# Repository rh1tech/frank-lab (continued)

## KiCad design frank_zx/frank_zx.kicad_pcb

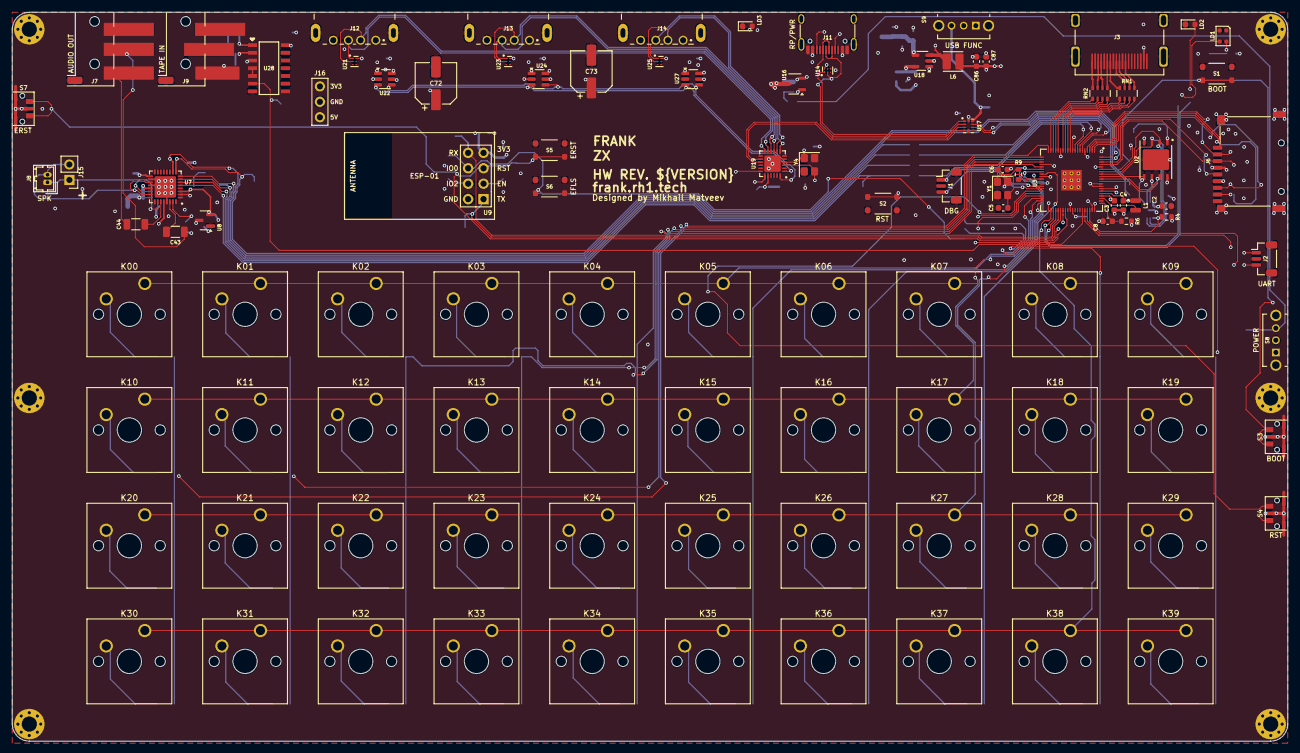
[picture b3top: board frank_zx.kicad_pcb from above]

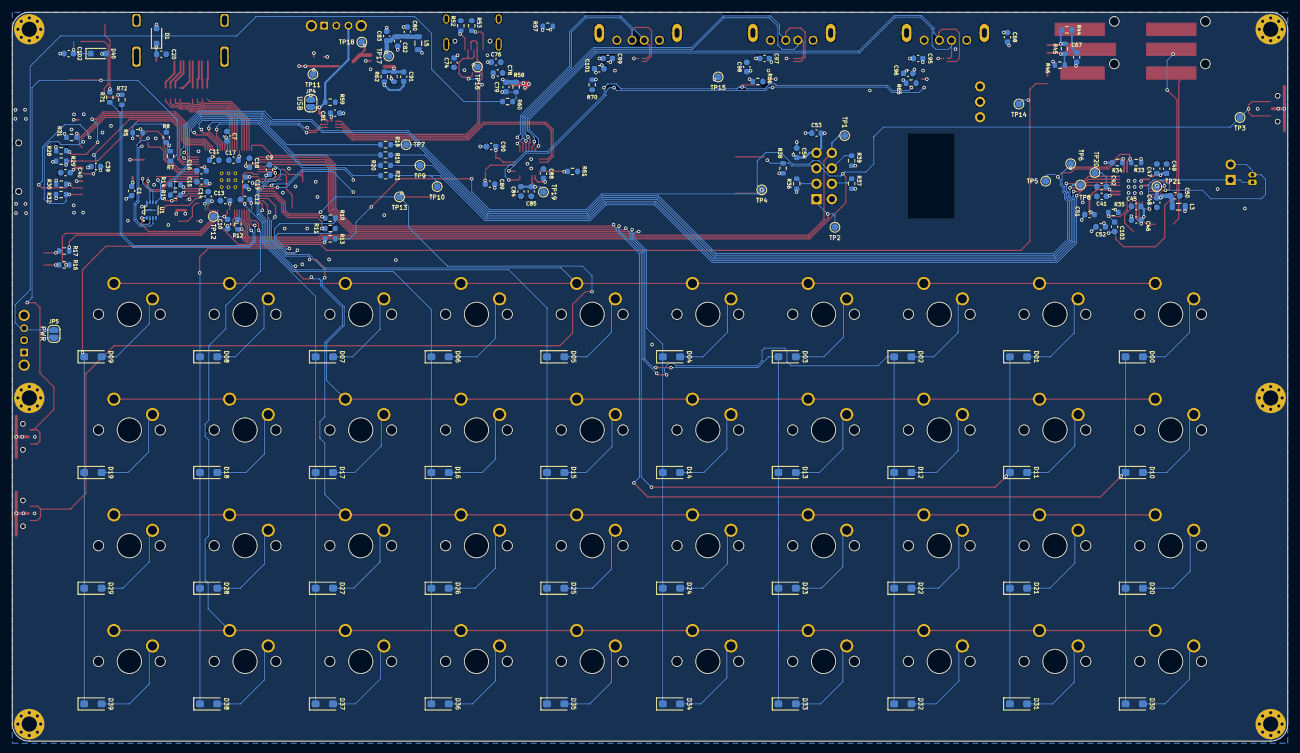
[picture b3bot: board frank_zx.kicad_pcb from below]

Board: 4 copper layers, 210.0 x 120.0 mm, 273 parts (164 on the bottom side), 179 nets.

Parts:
C1, C2, C7, C10, C11, C12, C13, C14, C15, C16, C17, C18, C19, C20, C40, C41, C42, C46, C49, C50, C54, C67, C68, C74, C79, C81, C83, C95, C97, C99, C102: 100nF; C_0603_1608Metric
C3, C4, C8, C9: 4.7uF; C_0603_1608Metric
C5, C6: 15pF; C_0603_1608Metric
C39, C45, C47, C48, C53, C76, C78, C80, C82, C84, C86, C87, C88, C96, C98, C101, C103: 10uF; C_0603_1608Metric
C43, C44: 100uF; C_1206_3216Metric
C51, C52, C85: 1uF; C_0603_1608Metric
C72, C73: 100uF; CP_Elec_6.3x6.0
C89, C90: 12pF; C_0603_1608Metric
C91: 22pF; C_0603_1608Metric
D00, D01, D02, D03, D04, D05, D06, D07, D08, D09, D10, D11, D12, D13, D14, D15, D16, D17, D18, D19, D20, D21, D22, D23, D24, D25, D26, D27, D28, D29, D30, D31, D32, D33, D34, D35, D36, D37, D38, D39: 1N4148W; D_SOD-123
D1, D40: 1N5819WS; D_SOD-323
H1, H2, H3, H4, H5, H6: MountingHole; MountingHole_2.5mm_Pad_Via
J1: Debug; JST_SH_1x03_P1.00mm_Vertical
J2: UART; JST_SH_1x03_P1.00mm_Vertical
J3: HDMI-001 19PCBTP; HDMI_Female
J6: 104031-0811; MicroSD_SMD_Long
J7: PJ-320D; AudioJack_3.5mm_PJ320D_AudioOut
J8: DF13-2P-1.25DSA; Hirose_DF13-02P-1.25DSA
J9: PJ-320D; AudioJack_3.5mm_PJ320D_TapeIn
J11: USB4215-03-A; USB_C_Receptacle
J12, J13, J14: AF 10.0 HC6.3; USB_A_Short
J15: Speaker; PinHeader_1x02_P2.54mm_Vertical
J16: PWR; PinHeader_1x03_P2.54mm
JP4: USB Debug; SolderJumper-2_P1.3mm_Open_RoundedPad1.0x1.5mm
JP5: PWR Debug; SolderJumper-2_P1.3mm_Open_RoundedPad1.0x1.5mm
K00, K01, K02, K03, K04, K05, K06, K07, K08, K09, K10, K11, K12, K13, K14, K15, K16, K17, K18, K19, K20, K21, K22, K23, K24, K25, K26, K27, K28, K29, K30, K31, K32, K33, K34, K35, K36, K37, K38, K39: MX; SW_Cherry_MX_1.00u_PCB
L1: 3.3µH; L_AOTA-B201610_2.0x1.6mm
L3, L5: 330R 2A; L_0805_2012Metric
L6: 2.2uH; L_Cenker_CKCS3015
LD1: WS2812B-2020; LED_WS2812B-2020_PLCC4_2.0x2.0mm
LD2: Blue; LED_0603_1608Metric
LD3: Green; LED_0603_1608Metric
R4, R5, R28, R29, R30, R31, R32, R35, R36, R37, R59, R60: 10K; R_0603_1608Metric
R6, R18, R19, R20, R21: 33R; R_0603_1608Metric
R7, R9, R57, R71: 1K; R_0603_1608Metric
R8: 0R; R_0603_1608Metric
R10, R11, R12, R13, R16, R17: 100R; R_0603_1608Metric
R14, R15: 27R; R_0603_1608Metric
R33, R34, R38, R39, R44, R61: 4.7K; R_0603_1608Metric
R45, R46, R58, R62, R65, R66, R70: 100K; R_0603_1608Metric
R52, R53: 5.1K; R_0603_1608Metric
R63: 22K; R_0603_1608Metric
R72: 330R; R_0603_1608Metric
RN1, RN2: 270R; R_Array_4x0603
S1: RP Boot; Button_SMD_3x4x2mm
S2: RP Reset; Button_SMD_3x4x2mm
S3: RP Boot; Button_SMD_TS1234VW
S4: RP Reset; Button_SMD_TS1234VW
S5: ESP Reset; Button_SMD_3x4x2mm
S6: ESP Flash; Button_SMD_3x4x2mm
S7: ESP Reset; Button_SMD_TS1234VW
S8, S9: SK12D07VG3NS; Switch_Slide_SK12D07VG3NS_PWR
TP1: GPIO36/TX; TestPoint_Pad_D1.2mm
TP2: GPIO37/RX; TestPoint_Pad_D1.2mm
TP3: GPIO38/ESP_RST; TestPoint_Pad_D1.2mm
TP4: GPIO39/ESP_BOOT; TestPoint_Pad_D1.2mm
TP5: GPIO2/SDA; TestPoint_Pad_D1.2mm
TP6: GPIO3/SCL; TestPoint_Pad_D1.2mm
TP7: GPIO8/MCLK; TestPoint_Pad_D1.2mm
TP8: GPIO9/BCLK; TestPoint_Pad_D1.2mm
TP9: GPIO10/WCLK; TestPoint_Pad_D1.2mm
TP10: GPIO11/DIN; TestPoint_Pad_D1.2mm
TP11: +3V3; TestPoint_Pad_D1.2mm
TP12: +1V1; TestPoint_Pad_D1.2mm
TP13: RUN; TestPoint_Pad_D1.2mm
TP14: GPIO44; TestPoint_Pad_D1.2mm
TP15: VBUS; TestPoint_Pad_D1.2mm
TP16: VBUS_IN; TestPoint_Pad_D1.2mm
TP17: +5V_BUCK; TestPoint_Pad_D1.2mm
TP18: LX; TestPoint_Pad_D1.2mm
TP19: VDD33; TestPoint_Pad_D1.2mm
TP20: +1V8; TestPoint_Pad_D1.2mm
TP21: +5V_SPK; TestPoint_Pad_D1.2mm
U1: APS6404L-3SQR-ZR; PSON50P200X300X50-9N
U2: W25Q128JVPIQ; WSON-8-1EP_6x5mm_P1.27mm_EP3.45x4.35mm
U3: RP2350B; RP2350-QFN-80_10x10_P0.4mm
U7: TLV320DAC3100IRHBR
U8: XC6206P182MR-G; SOT-23
U9: ESP-01v090; ESP-01S
U14, U21, U23, U25: TPD4S012DRYR
U16: AO3401A; SOT-23-3L_AOS
U17: TS3USB221RSER; UQFN-10
U18: SY8089AAAC; SOT-23-5
U19: CH334F; QFN-24-1EP_4x4mm_P0.5mm_EP2.7x2.7mm
U22, U24, U27: CH217K; SOT-23-6
U28: CD4069UBM; SOIC127P600X175-14N
Y1, Y4: 12 MHz; Crystal_SMD_3225-4Pin_3.2x2.5mm

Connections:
+1V1: C4.1, C7.1, C9.1, C10.1, L1.1, TP12.1, U3.10 (DVDD), U3.32 (DVDD), U3.51 (DVDD), U3.65 (VREG_FB)
+1V8: C42.2, C51.2, TP20.1, U7.3 (DVDD), U8.2 (VOUT)
+3V3: C1.1, C2.2, C3.1, C11.1, C12.1, C13.1, C14.1, C15.1, C16.1, C17.1, C18.1, C19.1, C39.2, C40.2, C41.1, C45.2, C46.2, C47.2, C49.2, C52.2, C53.1, C54.1, C68.1, C81.2, C86.1, C87.1, C91.1, J6.4 (VDD), J16.1, JP4.1 (A), L6.1, R4.2, R5.2, R6.1, R28.1, R29.1, R30.1, R31.2, R32.1, R33.2, R34.2, R35.2, R36.1, R37.1, R38.1, R39.1, R57.2, R62.1, S9.2, TP11.1, U1.8 (VDD), U2.8 (VCC), U3.5 (IOVDD), U3.15 (IOVDD), U3.24 (IOVDD), U3.29 (IOVDD), U3.41 (IOVDD), U3.50 (IOVDD), U3.59 (ADC_AVDD), U3.60 (IOVDD), U3.64 (VREG_VIN), U3.68 (USB_OTP_VDD), U3.69 (QSPI_IOVDD), U3.76 (IOVDD), U7.2 (IOVDD), U7.17 (AVDD), U7.28 (HPVDD), U8.3 (VIN), U9.7 (VCC), U17.10 (VCC), U28.14 (VDD)
/Audio/+5V_SPK: C48.2, C50.2, L3.1, TP21.1, U7.21 (SPKVDD_1), U7.24 (SPKVDD_2)
/Audio/CODEC_RST: C103.1, R35.1, U7.31 (~RESET)
/Audio/SPKM: J8.2, J15.2, U7.19 (SPKM_1), U7.23 (SPKM_2)
/Audio/SPKP: J8.1, J15.1, U7.22 (SPKP_1), U7.26 (SPKP_2)
/ESP01/CH_PD: R36.2, U9.3 (CH_PD)
/GPIO2/SDA: R34.1, TP5.1, U3.79 (GPIO2), U7.9 (SDA)
/GPIO3/SCL: R33.1, TP6.1, U3.80 (GPIO3), U7.10 (SCL)
/GPIO8/MCLK: R18.2, TP7.1, U7.8 (MCLK)
/GPIO9/BCLK: R19.2, TP8.1, U7.7 (BCLK)
/GPIO10/WCLK: R20.2, TP9.1, U7.6 (WCLK)
/GPIO11/DIN: R21.2, TP10.1, U7.5 (DIN)
/GPIO12/CLKN: RN1.4 (R4.1), U3.11 (GPIO12)
/GPIO13/CLKP: RN1.3 (R3.1), U3.12 (GPIO13)
/GPIO14/D0N: RN1.2 (R2.1), U3.13 (GPIO14)
/GPIO15/D0P: RN1.1 (R1.1), U3.14 (GPIO15)
/GPIO16/D1N: RN2.4 (R4.1), U3.16 (GPIO16)
/GPIO17/D1P: RN2.3 (R3.1), U3.17 (GPIO17)
/GPIO18/D2N: RN2.2 (R2.1), U3.18 (GPIO18)
/GPIO19/D2P: RN2.1 (R1.1), U3.19 (GPIO19)
/GPIO20/COL0: D00.1 (K), D10.1 (K), D20.1 (K), D30.1 (K), U3.20 (GPIO20)
/GPIO21/COL1: D01.1 (K), D11.1 (K), D21.1 (K), D31.1 (K), U3.21 (GPIO21)
/GPIO22/COL2: D02.1 (K), D12.1 (K), D22.1 (K), D32.1 (K), U3.22 (GPIO22)
/GPIO23/COL3: D03.1 (K), D13.1 (K), D23.1 (K), D33.1 (K), U3.23 (GPIO23)
/GPIO24/COL4: D04.1 (K), D14.1 (K), D24.1 (K), D34.1 (K), U3.25 (GPIO24)
/GPIO25/COL5: D05.1 (K), D15.1 (K), D25.1 (K), D35.1 (K), U3.26 (GPIO25)
/GPIO26/COL6: D06.1 (K), D16.1 (K), D26.1 (K), D36.1 (K), U3.27 (GPIO26)
/GPIO27/COL7: D07.1 (K), D17.1 (K), D27.1 (K), D37.1 (K), U3.28 (GPIO27)
/GPIO28/COL8: D08.1 (K), D18.1 (K), D28.1 (K), D38.1 (K), R10.2
/GPIO29/COL9: D09.1 (K), D19.1 (K), D29.1 (K), D39.1 (K), R11.2
/GPIO30/ROW0: K00.1, K01.1, K02.1, K03.1, K04.1, K05.1, K06.1, K07.1, K08.1, K09.1, U3.38 (GPIO30)
/GPIO31/ROW1: K10.1, K11.1, K12.1, K13.1, K14.1, K15.1, K16.1, K17.1, K18.1, K19.1, U3.39 (GPIO31)
/GPIO32/ROW2: K20.1, K21.1, K22.1, K23.1, K24.1, K25.1, K26.1, K27.1, K28.1, K29.1, U3.40 (GPIO32)
/GPIO33/ROW3: K30.1, K31.1, K32.1, K33.1, K34.1, K35.1, K36.1, K37.1, K38.1, K39.1, U3.42 (GPIO33)
/GPIO36/TX: TP1.1, U3.45 (GPIO36), U9.8 (URXD)
/GPIO37/RX: TP2.1, U3.46 (GPIO37), U9.1 (UTXD)
/GPIO38/ESP_RST: R12.2, R38.2, S5.1, S5.3, S7.1, TP3.1, U9.5 (RST)
/GPIO39/ESP_BOOT: R13.2, R39.2, S6.1, S6.3, TP4.1, U9.6 (GPIO0)
/RP2350B/BOOT: R7.2, S1.1, S1.3, S3.1
/RP2350B/D+: R14.1, U17.8 (D+)
/RP2350B/D-: R15.1, U17.7 (D-)
/RP2350B/GPIO44: TP14.1, U3.55 (GPIO44_ADC4), U28.6 (I=*C)
/RP2350B/GPIO45: R17.2, U3.56 (GPIO45_ADC5)
/RP2350B/GPIO46: R16.2, U3.57 (GPIO46_ADC6)
/RP2350B/GPIO47: R4.1, U1.1 (~CE), U3.58 (GPIO47_ADC7)
/RP2350B/LED: R71.1, U3.43 (GPIO34)
/RP2350B/QSPI_SCLK: U1.6 (SCLK), U2.6 (CLK), U3.71 (QSPI_SCLK)
/RP2350B/QSPI_SD0: U1.5 (SI/SIO(0)), U2.5 (DI_(IO0)), U3.72 (QSPI_SD0)
/RP2350B/QSPI_SD1: U1.2 (SO/SIO(1)), U2.2 (DO_(IO1)), U3.74 (QSPI_SD1)
/RP2350B/QSPI_SD2: U1.3 (SIO(2)), U2.3 (~WP_(IO2)), U3.73 (QSPI_SD2)
/RP2350B/QSPI_SD3: U1.7 (SIO(3)), U2.7 (~HOLD_OR_/RESET_(IO3)), U3.70 (QSPI_SD3)
/RP2350B/QSPI_SS: R7.1, R8.1, U3.75 (QSPI_SS)
/RP2350B/RGB_LED: R72.1, U3.44 (GPIO35)
/RP2350B/RUN: S2.1, S2.3, S4.1, TP13.1, U3.35 (RUN)
/RP2350B/SWCLK: J1.1 (Pin_3_3), U3.33 (SWCLK)
/RP2350B/SWD: J1.3 (Pin_1_1), U3.34 (SWD)
/RP2350B/VREG_AVDD: C8.1, R6.2, U3.61 (VREG_AVDD)
/RP2350B/VREG_LX: L1.2, U3.63 (VREG_LX)
/RP2350B/XIN: C5.1, U3.30 (XIN), Y1.3
/RP2350B/XOUT: R9.2, U3.31 (XOUT)
/SD/CD_DAT3/GPIO7: J6.2 (DAT3/CD), R28.2, U3.4 (GPIO7)
/SD/CLK/GPIO1: J6.5 (CLK), U3.78 (GPIO1)
/SD/CMD/GPIO0: J6.3 (CMD), R29.2, U3.77 (GPIO0)
/SD/DAT0/GPIO4: J6.7 (DAT0), R30.2, U3.1 (GPIO4)
/SD/DAT1/GPIO5: J6.8 (DAT1), R32.2, U3.2 (GPIO5)
/SD/DAT2/GPIO6: J6.1 (DAT2), R31.1, U3.3 (GPIO6)
/Tape/TAPE: C67.2, J9.T
/USB/+5V_BUCK: C80.1, C82.1, C83.1, L5.2, TP17.1, U18.1 (EN), U18.4 (IN)
/USB/DH+: U17.3 (2D+), U19.15 (DPU+)
/USB/DH-: U17.4 (2D-), U19.14 (DMU-)
/USB/DS1+: J12.3 (D+), U19.12 (DP1+), U21.1 (D+)
/USB/DS1-: J12.2 (D-), U19.11 (DM1-), U21.2 (D-_)
/USB/DS2+: J13.3 (D+), U19.10 (DP2+), U23.1 (D+)
/USB/DS2-: J13.2 (D-), U19.9 (DM2-), U23.2 (D-_)
/USB/DS3+: J14.3 (D+), U19.8 (DP3+), U25.1 (D+)
/USB/DS3-: J14.2 (D-), U19.7 (DM3-), U25.2 (D-_)
/USB/LX: L6.2, TP18.1, U18.3 (LX)
/USB/OVCUR: U19.1 (~OVCUR), U22.3 (FLAG#), U24.3 (FLAG#), U27.3 (FLAG#)
/USB/PWREN: U19.24 (~PWREN), U22.4 (EN#), U24.4 (EN#), U27.4 (EN#)
/USB/S: JP4.2 (B), R59.2, S9.3, U17.9 (S)
/USB/USB A Port 1/VBUS_P: C95.1, J12.1 (VBUS), U21.6 (VBUS), U22.1 (VOUT)
/USB/USB A Port 2/VBUS_P: C97.1, J13.1 (VBUS), U23.6 (VBUS), U24.1 (VOUT)
/USB/USB A Port 3/VBUS_P: C99.1, J14.1 (VBUS), U25.6 (VBUS), U27.1 (VOUT)
/USB/USBC_D+: J11.6 (DP1), J11.8 (DP2), U14.1 (D+), U17.1 (1D+)
/USB/USBC_D-: J11.5 (DN2), J11.7 (DN1), U14.2 (D-_), U17.2 (1D-)
/USB/VBUS_IN: C74.2, C76.2, C78.1, C79.2, J11.2 (VBUS), J11.11 (VBUS), R58.2, TP16.1, U14.6 (VBUS), U16.2 (S)
/USB/VDD33: C84.2, C85.2, TP19.1, U19.20 (VDD33_{LDO})
/USB/XTAL_N: C89.1, U19.3 (XO), Y4.3
/USB/XTAL_P: C90.1, U19.4 (XI), Y4.1
GND: C1.2, C2.1, C3.2, C4.2, C5.2, C6.2, C7.2, C8.2, C9.2, C10.2, C11.2, C12.2, C13.2, C14.2, C15.2, C16.2, C17.2, C18.2, C19.2, C20.2, C39.1, C40.1, C41.2, C42.1, C45.1, C46.1, C47.1, C48.1, C49.1, C50.1, C51.1, C52.1, C53.2, C54.2, C68.2, C72.2, C73.2, C74.1, C76.1, C78.2, C80.2, C81.1, C82.2, C83.2, C84.1, C85.1, C86.2, C87.2, C88.1, C89.2, C90.2, C95.2, C96.1, C97.2, C98.1, C99.2, C101.1, C102.2, C103.2, H1.1 (1_1), H2.1 (1_1), H3.1 (1_1), H4.1 (1_1), H5.1 (1_1), H6.1 (1_1), J1.2 (Pin_2_2), J2.2 (Pin_2_2), J3.2 (G_D2), J3.5 (G_D1), J3.8 (G_D0), J3.11 (G_CLK), J3.17 (G_DDC/CEC), J3.20 (SHIELD1), J3.21 (SHIELD2), J3.22 (SHIELD3), J3.23 (SHIELD4), J6.6 (VSS), J6.SH (SHIELD), J7.S, J9.S, J11.1 (GND), J11.12 (GND), J11.13 (SHIELD), J12.4 (GND), J12.5 (Shield), J13.4 (GND), J13.5 (Shield), J14.4 (GND), J14.5 (Shield), J16.2, JP5.1 (A), LD1.2 (VSS), LD2.1 (K), LD3.1 (K), R52.1, R53.1, R59.1, R61.2, R63.2, R65.1, R66.1, R70.1, S1.2, S1.4, S2.2, S2.4, S3.2, S3.3 (GND), S4.2, S4.3 (GND), S5.2, S5.4, S6.2, S6.4, S7.2, S7.3 (GND), S8.2, U1.4 (VSS), U1.9 (EXP), U2.4 (GND_1), U2.9 (GND_2), U3.62 (VREG_PGND), U3.81 (GND), U7.1 (IOVSS), U7.16 (AVSS), U7.18 (DVSS), U7.20 (SPKVSS_1), U7.25 (SPKVSS_2), U7.29 (HPVSS), U7.33 (EP), U8.1 (VSS), U9.2 (GND), U14.4 (GND), U17.5 (GND), U17.6 (~OE), U18.2 (GND), U19.25 (GND), U21.4 (GND), U22.2 (GND), U23.4 (GND), U24.2 (GND), U25.4 (GND), U27.2 (GND), U28.7 (VSS), U28.9 (D), U28.11 (E), U28.13 (F), Y1.2, Y1.4, Y4.2, Y4.4
unnamed: C6.1, R9.1, Y1.1
unnamed: C43.1, J7.R
unnamed: C44.1, J7.T
unnamed: C67.1, R44.2
unnamed: D00.2 (A), K00.2
unnamed: D01.2 (A), K01.2
unnamed: C20.1, D1.1 (K), J3.18 (+5V)
unnamed: D02.2 (A), K02.2
unnamed: D03.2 (A), K03.2
unnamed: D04.2 (A), K04.2
unnamed: D05.2 (A), K05.2
unnamed: D06.2 (A), K06.2
unnamed: D07.2 (A), K07.2
unnamed: D08.2 (A), K08.2
unnamed: D09.2 (A), K09.2
unnamed: D10.2 (A), K10.2
unnamed: D11.2 (A), K11.2
unnamed: D12.2 (A), K12.2
unnamed: D13.2 (A), K13.2
unnamed: D14.2 (A), K14.2
unnamed: D15.2 (A), K15.2
unnamed: D16.2 (A), K16.2
unnamed: D17.2 (A), K17.2
unnamed: D18.2 (A), K18.2
unnamed: D19.2 (A), K19.2
unnamed: D20.2 (A), K20.2
unnamed: D21.2 (A), K21.2
unnamed: D22.2 (A), K22.2
unnamed: D23.2 (A), K23.2
unnamed: D24.2 (A), K24.2
unnamed: D25.2 (A), K25.2
unnamed: D26.2 (A), K26.2
unnamed: D27.2 (A), K27.2
unnamed: D28.2 (A), K28.2
unnamed: D29.2 (A), K29.2
unnamed: D30.2 (A), K30.2
unnamed: D31.2 (A), K31.2
unnamed: D32.2 (A), K32.2
unnamed: D33.2 (A), K33.2
unnamed: D34.2 (A), K34.2
unnamed: D35.2 (A), K35.2
unnamed: D36.2 (A), K36.2
unnamed: D37.2 (A), K37.2
unnamed: D38.2 (A), K38.2
unnamed: D39.2 (A), K39.2
unnamed: C102.1, D40.1 (K), LD1.4 (VDD)
unnamed: J2.1 (Pin_3_3), R17.1
unnamed: J2.3 (Pin_1_1), R16.1
unnamed: J3.12 (CLKN), RN1.5 (R4.2)
unnamed: J3.10 (CLKP), RN1.6 (R3.2)
unnamed: J3.9 (D0N), RN1.7 (R2.2)
unnamed: J3.7 (D0P), RN1.8 (R1.2)
unnamed: J3.6 (D1N), RN2.5 (R4.2)
unnamed: J3.4 (D1P), RN2.6 (R3.2)
unnamed: J3.3 (D2N), RN2.7 (R2.2)
unnamed: J3.1 (D2P), RN2.8 (R1.2)
unnamed: J11.4 (CC1), R52.2
unnamed: J11.10 (CC2), R53.2
unnamed: JP5.2 (B), R60.2, S8.3
unnamed: LD1.3 (DIN), R72.2
unnamed: LD2.2 (A), R71.2
unnamed: LD3.2 (A), R57.1
unnamed: R5.1, R8.2, U2.1 (~CS)
unnamed: R18.1, U3.6 (GPIO8)
unnamed: R19.1, U3.7 (GPIO9)
unnamed: R20.1, U3.8 (GPIO10)
unnamed: R21.1, U3.9 (GPIO11)
unnamed: R10.1, U3.36 (GPIO28)
unnamed: R11.1, U3.37 (GPIO29)
unnamed: R12.1, U3.47 (GPIO38)
unnamed: R13.1, U3.48 (GPIO39)
unnamed: R15.2, U3.66 (USB_DM)
unnamed: R14.2, U3.67 (USB_DP)
unnamed: C44.2, U7.27 (HPL)
unnamed: C43.2, U7.30 (HPR)
unnamed: R37.2, U9.4 (GPIO2)
unnamed: C79.1, R58.1, R60.1, U16.1 (G)
unnamed: C91.2, R62.2, R63.1, U18.5 (FB)
unnamed: R61.1, U19.18 (PSELF)
unnamed: R65.2, U22.5 (ISET)
unnamed: R66.2, U24.5 (ISET)
unnamed: R70.2, U27.5 (ISET)
unnamed: R44.1, R45.2, U28.1 (A)
unnamed: R46.1, U28.3 (B)
unnamed: U28.4 (H=*B), U28.5 (C)
unnamed: R45.1, R46.2, U28.2 (G-*A)
VBUS: C72.1, C73.1, C88.2, C96.2, C98.2, C101.2, D1.2 (A), D40.2 (A), J16.3, L3.2, L5.1, TP15.1, U16.3 (D), U19.19 (V5), U22.6 (VIN), U24.6 (VIN), U27.6 (VIN)

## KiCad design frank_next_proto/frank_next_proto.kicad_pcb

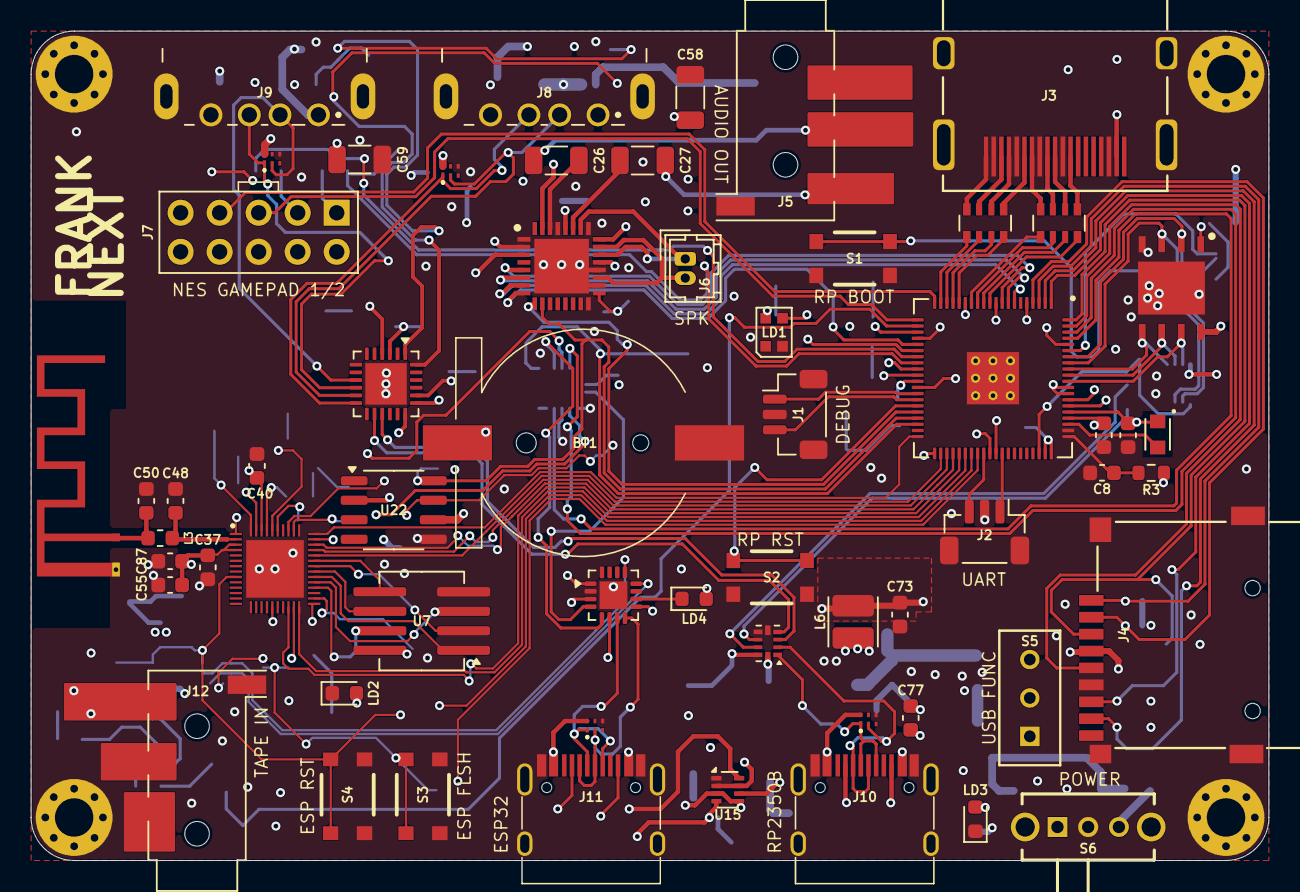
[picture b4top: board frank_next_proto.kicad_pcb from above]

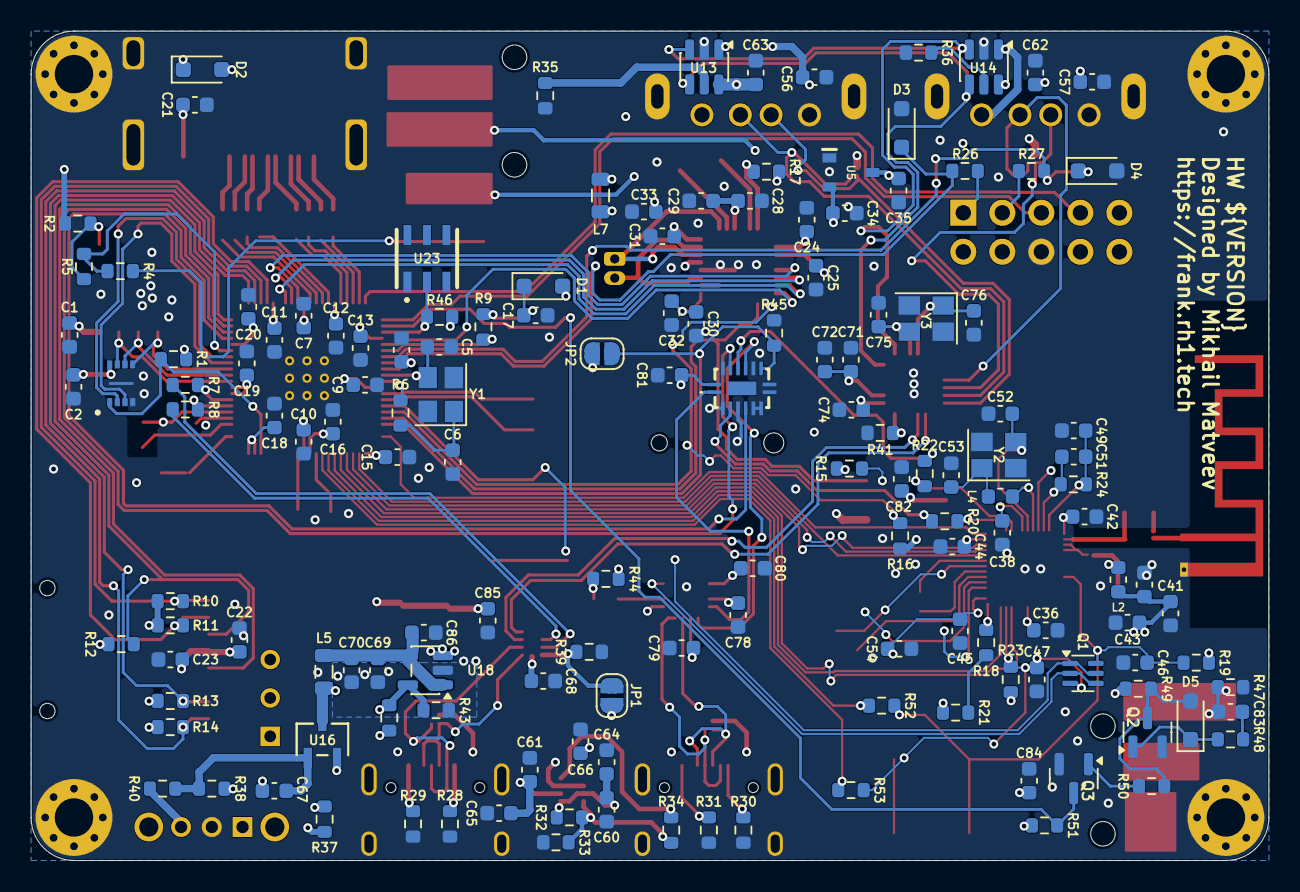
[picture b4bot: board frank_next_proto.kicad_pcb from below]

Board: 4 copper layers, 80.6 x 54.0 mm, 211 parts (148 on the bottom side), 160 nets.

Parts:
AE1: Antenna; Antenna_2.4GHz
BT1: CR1220; Battery_CR1220
C1, C2, C7, C10, C11, C12, C13, C14, C15, C16, C17, C18, C19, C20, C21, C23, C24, C25, C29, C32, C33, C37, C39, C40, C42, C44, C45, C56, C57, C60, C61, C67, C68, C78, C79, C80, C81, C82, C83, C84, C86: 100nF; C_0603_1608Metric
C3, C4, C8, C9: 4.7uF; C_0603_1608Metric
C5, C6: 15pF; C_0603_1608Metric
C22, C28, C30, C31, C41, C55, C62, C63, C64, C65, C66, C69, C70, C71, C73, C74, C85, C87: 10uF; C_0603_1608Metric
C26, C27, C58, C59: 100uF; C_1206_3216Metric
C34, C35, C36, C43, C46, C54, C72: 1uF; C_0603_1608Metric
C38: 100pF; C_0603_1608Metric
C47: 1nF; C_0603_1608Metric
C48: 1.5pF; C_0603_1608Metric
C49: 10nF; C_0603_1608Metric
C50: 2.4pF; C_0603_1608Metric
C51: 3.3nF; C_0603_1608Metric
C52, C53, C75, C76: 12pF; C_0603_1608Metric
C77: 22pF; C_0603_1608Metric
D1, D2: 1N5819WS; D_SOD-323
D3, D4: 3V3; D_SOD-323
D5: 1N4148; D_SOD-323
H1, H2, H3, H4: MountingHole; MountingHole_2.5mm_Pad_Via
J1: Debug; JST_SH_1x03_P1.00mm_Vertical
J2: UART; JST_SH_1x03_P1.00mm_Vertical
J3: HDMI-001 19PCBTP; HDMI_Female
J4: 104031-0811; MicroSD_SMD_Long
J5: PJ-320D; AudioJack_3.5mm_PJ320D_AudioOut
J6: Speaker; JST_GH_1x02_P1.25mm
J7: NES Gamepad 1/2; PinHeader_2x05_P2.54mm_Vertical
J8, J9: AF 10.0 HC6.3; USB_A_Short
J10, J11: USB4215-03-A; USB_C_Receptacle
J12: PJ-320D; AudioJack_3.5mm_PJ320D_TapeIn
JP1: USB Debug; SolderJumper-2_P1.3mm_Open_RoundedPad1.0x1.5mm
JP2: ESP Debug; SolderJumper-2_P1.3mm_Open_RoundedPad1.0x1.5mm
L1: 3.3µH; L_Murata_LQH2MCN_2.0x1.6mm
L2: 2nH; L_0603_1608Metric
L3: 2.7nH/0R; L_0603_1608Metric
L4: 24nH/0R; L_0603_1608Metric
L5, L7: 330R 2A; L_0805_2012Metric
L6: 2.2uH; L_Cenker_CKCS3015
LD1: WS2812B-2020; LED_WS2812B-2020_PLCC4_2.0x2.0mm
LD2: Blue; LED_0603_1608Metric
LD3: Green; LED_0603_1608Metric
LD4: Orange; LED_0603_1608Metric
Q1: UMH3N; SOT-363
Q2, Q3: BC850; SOT-23
R1, R2, R10, R11, R12, R13, R14, R17, R19, R23, R39, R45, R48, R49, R50: 10K; R_0603_1608Metric
R3: 33R; R_0603_1608Metric
R4, R6, R26, R27, R37, R40, R44, R51, R52, R53: 1K; R_0603_1608Metric
R5, R18: 0R; R_0603_1608Metric
R7, R8: 27R; R_0603_1608Metric
R9, R20, R22: 330R; R_0603_1608Metric
R15, R16, R41, R46: 4.7K; R_0603_1608Metric
R21: 220R; R_0603_1608Metric
R24: 20K; R_0603_1608Metric
R28, R29, R30, R31: 5.1K; R_0603_1608Metric
R32: 300K; R_0603_1608Metric
R33, R35, R36, R38, R42: 100K; R_0603_1608Metric
R34: 1M; R_0603_1608Metric
R43: 22K; R_0603_1608Metric
R47: 100R; R_0603_1608Metric
RN1, RN2: 270R; R_Array_4x0603
S1: RP Boot; Button_SMD_3x4x2mm
S2: RP Reset; Button_SMD_3x4x2mm
S3: ESP Flash; Button_SMD_3x4x2mm
S4: ESP Reset; Button_SMD_3x4x2mm
S5: SS12D00; Switch_Slide_SS12D00
S6: SK12D07VG3NS; Switch_Slide_SK12D07VG3NS_PWR
U1: APS6404L-3SQR-ZR; PSON50P200X300X50-9N
U2: W25Q128JVPIQ; WSON-8-1EP_6x5mm_P1.27mm_EP3.45x4.35mm
U3: RP2350B; RP2350-QFN-80_10x10_P0.4mm
U4: TLV320DAC3100IRHBR
U5: XC6206P182MR-G
U6: ESP32-D0WD-V3; QFN-48-1EP_5x5mm_P0.35mm_EP3.75x3.75mm
U7: W25Q32JVSIQ; SOIC-8_Longer
U9, U10, U11, U12: TPD4S012DRYR
U13, U14: CH217K; SOT-23-6
U15: TPS2116DRL; SOT-583-8
U16: AO3401A; SOT-23-3L_AOS
U17: TS3USB221RSER; UQFN-10
U18: SY8089AAAC; SOT-23-5
U19: CH334F; QFN-24-1EP_4x4mm_P0.5mm_EP2.7x2.7mm
U20: CH343P; WCH_QFN-16-1EP_3x3mm_P0.5mm_EP1.8x1.8mm
U21: 74HC4052BQ; 74HC4052BQ115
U22: DS3231MZ; SO-8_3.9x4.9mm_P1.27mm
U23: DS2401P+; TSOC-6
Y1, Y3: 12 MHz; Crystal_SMD_3225-4Pin_3.2x2.5mm
Y2: 40 MHz; Crystal_SMD_3225-4Pin_3.2x2.5mm

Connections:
+1V1: C4.1, C7.1, C9.1, C10.1, L1.1, U3.10 (DVDD), U3.32 (DVDD), U3.51 (DVDD), U3.65 (VREG_FB)
+1V8: C25.2, C34.2, U4.3 (DVDD), U5.2 (VOUT)
+3.3VP: C37.1, C55.1, C87.1, L2.2, U6.3 (VDD3P3_1), U6.4 (VDD3P3_2)
+3V3: C1.1, C2.2, C3.1, C11.1, C12.1, C13.1, C14.1, C15.1, C16.1, C18.1, C19.1, C20.1, C22.2, C23.2, C24.1, C28.2, C29.2, C30.2, C32.2, C35.2, C36.1, C38.1, C39.1, C40.1, C41.1, C42.1, C43.1, C44.1, C68.2, C73.1, C77.1, C80.2, C81.2, C82.1, C84.2, C85.1, J4.4 (VDD), JP1.1 (A), JP2.1 (A), L2.1, L6.1, R1.2, R2.2, R3.1, R10.1, R11.1, R12.1, R13.1, R14.1, R15.2, R16.2, R17.2, R19.2, R23.2, R37.2, R42.1, R44.2, R46.1, R49.1, R51.1, S5.2, U1.8 (VDD), U2.8 (VCC), U3.5 (IOVDD), U3.15 (IOVDD), U3.24 (IOVDD), U3.29 (IOVDD), U3.41 (IOVDD), U3.50 (IOVDD), U3.59 (ADC_AVDD), U3.60 (IOVDD), U3.64 (VREG_VIN), U3.68 (USB_OTP_VDD), U3.69 (QSPI_IOVDD), U3.76 (IOVDD), U4.2 (IOVDD), U4.17 (AVDD), U4.28 (HPVDD), U5.3 (VIN), U6.1 (VDDA_1), U6.19 (VDD3P3_RTC), U6.37 (VDD3P3_CPU), U6.43 (VDDA_2), U6.46 (VDDA_3), U17.10 (VCC), U20.1 (VIO), U21.16 (VCC_1), U22.2 (VCC)
/Audio/+5V_SPK: C31.2, C33.2, L7.1, U4.21 (SPKVDD_1), U4.24 (SPKVDD_2)
/Audio/SPKM: J6.2, U4.19 (SPKM_1), U4.23 (SPKM_2)
/Audio/SPKP: J6.1, U4.22 (SPKP_1), U4.26 (SPKP_2)
/CH343P/DTR: Q1.2 (B1), Q1.4 (E2), U20.12 (~DTR)
/CH343P/RTS: Q1.1 (E1), Q1.5 (B2), U20.13 (~RTS)
/CH343P/RXD: U20.5 (RXD), U21.12 (1Y0)
/CH343P/TXD: U20.4 (TXD), U21.1 (2Y0)
/CS (GPIO33/GPIO5): U3.42 (GPIO33), U6.34 (GPIO5)
/D+: R7.1, U17.8 (D+)
/D-: R8.1, U17.7 (D-)
/ESP32/ANT: AE1.1 (A), C50.1, L3.1
/ESP32/CAP1: C49.1, C51.1, R24.2, U6.48 (CAP1)
/ESP32/CAP2: C51.2, R24.1, U6.47 (CAP2)
/ESP32/GPIO16: R18.2, R21.2
/ESP32/LNA_IN: C48.1, L3.2, U6.2 (LNA_IN)
/ESP32/SCK/CLK: U6.31 (SD_CLK), U7.6 (CLK)
/ESP32/SCS/CMD: U6.30 (SD_CMD), U7.1 (~CS)
/ESP32/SDI/SD1: U6.33 (SD_DATA_1), U7.5 (DI(IO0))
/ESP32/SDO/SD0: U6.32 (SD_DATA_0), U7.2 (DO(IO1))
/ESP32/SHD/SD2: U6.28 (SD_DATA_2), U7.7 (IO3)
/ESP32/SWP/SD3: U6.29 (SD_DATA_3), U7.3 (IO2)
/ESP32/U0RXD: R20.2, U6.40 (U0RXD)
/ESP32/U0TXD: R22.2, U6.41 (U0TXD)
/ESP32/VDD_SDIO: C45.2, C54.1, U6.26 (VDD_SDIO), U7.8 (VCC)
/ESP32/XTAL_N: C52.1, U6.44 (XTAL_N), Y2.3
/ESP32/XTAL_P: L4.1, U6.45 (XTAL_P)
/ESP Multiplexer/1Z: R22.1, U21.13 (1Z)
/ESP Multiplexer/2Z: R20.1, U21.3 (2Z)
/GPIO0/RXD: U3.77 (GPIO0), U21.5 (2Y1)
/GPIO1/TXD: U3.78 (GPIO1), U21.14 (1Y1)
/GPIO2/CLK: J4.5 (CLK), U3.79 (GPIO2)
/GPIO3/CMD: J4.3 (CMD), R12.2, U3.80 (GPIO3)
/GPIO4/DAT0: J4.7 (DAT0), R13.2, U3.1 (GPIO4)
/GPIO5/DAT1: J4.8 (DAT1), R14.2, U3.2 (GPIO5)
/GPIO6/DAT2: J4.1 (DAT2), R10.2, U3.3 (GPIO6)
/GPIO7/DAT3: J4.2 (DAT3/CD), R11.2, U3.4 (GPIO7)
/GPIO9/BCLK: U3.7 (GPIO9), U4.7 (BCLK)
/GPIO10/WCLK: U3.8 (GPIO10), U4.6 (WCLK)
/GPIO11/DIN: U3.9 (GPIO11), U4.5 (DIN)
/GPIO12/CLKN: RN1.4 (R4.1), U3.11 (GPIO12)
/GPIO13/CLKP: RN1.3 (R3.1), U3.12 (GPIO13)
/GPIO14/D0N: RN1.2 (R2.1), U3.13 (GPIO14)
/GPIO15/D0P: RN1.1 (R1.1), U3.14 (GPIO15)
/GPIO16/D1N: RN2.4 (R4.1), U3.16 (GPIO16)
/GPIO17/D1P: RN2.3 (R3.1), U3.17 (GPIO17)
/GPIO18/D2N: RN2.2 (R2.1), U3.18 (GPIO18)
/GPIO19/D2P: RN2.1 (R1.1), U3.19 (GPIO19)
/GPIO20: J7.4, U3.20 (GPIO20)
/GPIO21: J7.3, U3.21 (GPIO21)
/GPIO22/LOAD_IN: Q3.3 (C), R51.2, U3.22 (GPIO22)
/GPIO23/DATA: R46.2, U3.23 (GPIO23), U23.2 (DATA)
/GPIO24/MCLK: U3.25 (GPIO24), U4.8 (MCLK)
/GPIO26: D4.1 (K), R27.1, U3.27 (GPIO26)
/GPIO27: D3.1 (K), R26.1, U3.28 (GPIO27)
/GPIO28/SDA: R16.1, U3.36 (GPIO28), U4.9 (SDA), U22.7 (SDA)
/GPIO29/SCL: R15.1, U3.37 (GPIO29), U4.10 (SCL), U22.8 (SCL)
/GPIO30/S0: JP2.2 (B), R45.1, U3.38 (GPIO30), U21.10 (S0)
/GPIO38/CHIP_PU: C46.1, Q1.6 (C1), R19.1, R52.2, S4.1, S4.3, U6.9 (CHIP_PU)
/GPIO39/GPIO0: C47.1, Q1.3 (C2), R23.1, R53.2, S3.1, S3.3, U6.23 (GPIO0)
/HS (GPIO36/GPIO2): U3.45 (GPIO36), U6.22 (GPIO2)
/MISO (GPIO32/GPIO19): U3.40 (GPIO32), U6.38 (GPIO19)
/MOSI (GPIO35/GPIO23): U3.44 (GPIO35), U6.36 (GPIO23)
/NES Gamepad/G_DATA1: J7.2, R27.2
/NES Gamepad/G_DATA2: J7.1, R26.2
/READY (GPIO37/GPIO4): U3.46 (GPIO37), U6.24 (GPIO4)
/RP2350B/BOOT: R4.2, S1.1, S1.3
/RP2350B/GPIO40/UART_1: J2.1, U3.49 (GPIO40_ADC0)
/RP2350B/GPIO41/UART_3: J2.3, U3.52 (GPIO41_ADC1)
/RP2350B/GPIO47: R1.1, U1.1 (~CE), U3.58 (GPIO47_ADC7)
/RP2350B/QSPI_SCLK: U1.6 (SCLK), U2.6 (CLK), U3.71 (QSPI_SCLK)
/RP2350B/QSPI_SD0: U1.5 (SI/SIO(0)), U2.5 (DI_(IO0)), U3.72 (QSPI_SD0)
/RP2350B/QSPI_SD1: U1.2 (SO/SIO(1)), U2.2 (DO_(IO1)), U3.74 (QSPI_SD1)
/RP2350B/QSPI_SD2: U1.3 (SIO(2)), U2.3 (~WP_(IO2)), U3.73 (QSPI_SD2)
/RP2350B/QSPI_SD3: U1.7 (SIO(3)), U2.7 (~HOLD_OR_/RESET_(IO3)), U3.70 (QSPI_SD3)
/RP2350B/QSPI_SS: R4.1, R5.1, U3.75 (QSPI_SS)
/RP2350B/RUN: S2.1, S2.3, U3.35 (RUN)
/RP2350B/SWCLK: J1.3, U3.33 (SWCLK)
/RP2350B/SWD: J1.1, U3.34 (SWD)
/RP2350B/VREG_AVDD: C8.1, R3.2, U3.61 (VREG_AVDD)
/RP2350B/VREG_LX: L1.2, U3.63 (VREG_LX)
/RP2350B/XIN: C5.1, U3.30 (XIN), Y1.3
/RP2350B/XOUT: R6.2, U3.31 (XOUT)
/SCK (GPIO34/GPIO18): U3.43 (GPIO34), U6.35 (GPIO18)
/Tape In/TAPE: C83.1, J12.T, R47.1
/UD+: J11.6 (DP1), J11.8 (DP2), U12.1 (D+), U20.7 (UD+)
/UD-: J11.5 (DN2), J11.7 (DN1), U12.2 (D-_), U20.8 (UD-)
/USB/+5V_BUCK: C69.1, C70.1, C86.1, L5.2, U18.1 (EN), U18.4 (IN)
/USB/D2+: J10.6 (DP1), J10.8 (DP2), U11.1 (D+), U17.1 (1D+)
/USB/D2-: J10.5 (DN2), J10.7 (DN1), U11.2 (D-_), U17.2 (1D-)
/USB/DH+: U17.3 (2D+), U19.15 (DPU+)
/USB/DH-: U17.4 (2D-), U19.14 (DMU-)
/USB/DS1+: J8.3 (D+), U9.1 (D+), U19.12 (DP1+)
/USB/DS1-: J8.2 (D-), U9.2 (D-_), U19.11 (DM1-)
/USB/DS2+: J9.3 (D+), U10.1 (D+), U19.10 (DP2+)
/USB/DS2-: J9.2 (D-), U10.2 (D-_), U19.9 (DM2-)
/USB/OVCUR: U13.3 (FLAG#), U14.3 (FLAG#), U19.1 (~OVCUR)
/USB/PWREN: U13.4 (EN#), U14.4 (EN#), U19.24 (~PWREN)
/USB/S: JP1.2 (B), R39.2, S5.3, U17.9 (S)
/USB/ST: R34.2, U15.8 (ST)
/USB/VBUS_IN: C66.1, C67.2, R38.2, U15.2 (VOUT), U15.7 (VOUT), U16.2 (S)
/USB/VBUS_IN1: C60.2, C64.2, J11.2 (VBUS), J11.11 (VBUS), R32.2, U12.6 (VBUS), U15.3 (VIN1), U15.5 (MODE)
/USB/VBUS_IN2: C61.2, C65.2, J10.2 (VBUS), J10.11 (VBUS), U11.6 (VBUS), U15.6 (VIN2)
/USB/VBUS_P1: C56.1, C58.1, J8.1 (VBUS), U9.6 (VBUS), U13.1 (VOUT)
/USB/VBUS_P2: C57.1, C59.1, J9.1 (VBUS), U10.6 (VBUS), U14.1 (VOUT)
/USB/VDD33: C71.2, C72.2, U19.20 (VDD33_{LDO})
/USB/XTAL_N: C75.1, U19.3 (XO), Y3.3
/USB/XTAL_P: C76.1, U19.4 (XI), Y3.1
GND: AE1.2 (Shield), BT1.2 (-), C1.2, C2.1, C3.2, C4.2, C5.2, C6.2, C7.2, C8.2, C9.2, C10.2, C11.2, C12.2, C13.2, C14.2, C15.2, C16.2, C17.2, C18.2, C19.2, C20.2, C21.2, C22.1, C23.1, C24.2, C25.1, C28.1, C29.1, C30.1, C31.1, C32.1, C33.1, C34.1, C35.1, C36.2, C37.2, C38.2, C39.2, C40.2, C41.2, C42.2, C43.2, C44.2, C45.1, C46.2, C47.2, C48.2, C49.2, C50.2, C52.2, C53.2, C54.2, C55.2, C56.2, C57.2, C58.2, C59.2, C60.1, C61.1, C62.1, C63.1, C64.1, C65.1, C66.2, C68.1, C69.2, C70.2, C71.1, C72.1, C73.2, C74.1, C75.2, C76.2, C78.1, C79.1, C80.1, C81.1, C82.2, C84.1, C85.2, C86.2, C87.2, D3.2 (A), D4.2 (A), H1.1 (1_1), H2.1 (1_1), H3.1 (1_1), H4.1 (1_1), J1.2, J2.2, J3.2 (G_D2), J3.5 (G_D1), J3.8 (G_D0), J3.11 (G_CLK), J3.17 (G_DDC/CEC), J3.20 (SHIELD1), J3.21 (SHIELD2), J3.22 (SHIELD3), J3.23 (SHIELD4), J4.6 (VSS), J4.SH (SHIELD), J5.S, J7.8, J8.4 (GND), J8.5 (Shield), J9.4 (GND), J9.5 (Shield), J10.1 (GND), J10.12 (GND), J10.13 (SHIELD), J11.1 (GND), J11.12 (GND), J11.13 (SHIELD), J12.S, LD1.2 (VSS), LD2.1 (K), LD3.1 (K), Q2.2 (E), Q3.2 (E), R28.1, R29.1, R30.1, R31.1, R33.1, R35.1, R36.1, R39.1, R41.2, R43.2, R45.2, R47.2, S1.2, S1.4, S2.2, S2.4, S3.2, S3.4, S4.2, S4.4, S6.2, U1.4 (VSS), U1.9 (EXP), U2.4 (GND_1), U2.9 (GND_2), U3.62 (VREG_PGND), U3.81 (GND), U4.1 (IOVSS), U4.16 (AVSS), U4.18 (DVSS), U4.20 (SPKVSS_1), U4.25 (SPKVSS_2), U4.29 (HPVSS), U4.33 (EP), U5.1 (VSS), U6.49 (GND), U7.4 (GND), U9.4 (GND), U10.4 (GND), U11.4 (GND), U12.4 (GND), U13.2 (GND), U14.2 (GND), U15.1 (GND), U17.5 (GND), U17.6 (~OE), U18.2 (GND), U19.25 (GND), U20.2 (GND), U20.17 (GND_EPAD), U21.2 (2Y2), U21.4 (2Y3), U21.6 (~E), U21.7 (VEE), U21.8 (GND), U21.9 (S1), U21.11 (1Y3), U21.15 (1Y2), U22.5 (GND), U23.1 (GND), Y1.2, Y1.4, Y2.2, Y2.4, Y3.2, Y3.4
unnamed: BT1.1 (+), U22.6 (VBAT)
unnamed: C6.1, R6.1, Y1.1
unnamed: C26.1, J5.R
unnamed: C27.1, J5.T
unnamed: C53.1, L4.2, Y2.1
unnamed: C83.2, R48.1
unnamed: C17.1, D1.1 (K), LD1.4 (VDD)
unnamed: C21.1, D2.1 (K), J3.18 (+5V)
unnamed: D5.2 (A), Q2.3 (C), R49.2, R50.1
unnamed: D5.1 (K), Q2.1 (B), R48.2
unnamed: J3.12 (CLKN), RN1.5 (R4.2)
unnamed: J3.10 (CLKP), RN1.6 (R3.2)
unnamed: J3.9 (D0N), RN1.7 (R2.2)
unnamed: J3.7 (D0P), RN1.8 (R1.2)
unnamed: J3.6 (D1N), RN2.5 (R4.2)
unnamed: J3.4 (D1P), RN2.6 (R3.2)
unnamed: J3.3 (D2N), RN2.7 (R2.2)
unnamed: J3.1 (D2P), RN2.8 (R1.2)
unnamed: J10.4 (CC1), R28.2
unnamed: J10.10 (CC2), R29.2
unnamed: J11.4 (CC1), R30.2
unnamed: J11.10 (CC2), R31.2
unnamed: LD1.3 (DIN), R9.1
unnamed: LD2.2 (A), R21.1
unnamed: LD3.2 (A), R37.1
unnamed: LD4.2 (A), R44.1
unnamed: LD4.1 (K), U20.10 (~ACT)
unnamed: Q3.1 (B), R50.2
unnamed: R40.2, S6.3
unnamed: R2.1, R5.2, U2.1 (~CS)
unnamed: R9.2, U3.26 (GPIO25)
unnamed: R52.1, U3.47 (GPIO38)
unnamed: R53.1, U3.48 (GPIO39)
unnamed: R8.2, U3.66 (USB_DM)
unnamed: R7.2, U3.67 (USB_DP)
unnamed: C27.2, U4.27 (HPL)
unnamed: C26.2, U4.30 (HPR)
unnamed: R17.1, U4.31 (~RESET)
unnamed: R18.1, U6.25 (GPIO16)
unnamed: R35.2, U13.5 (ISET)
unnamed: R36.2, U14.5 (ISET)
unnamed: R32.1, R33.2, R34.1, U15.4 (PR1)
unnamed: C67.1, R38.1, R40.1, U16.1 (G)
unnamed: C77.2, R42.2, R43.1, U18.5 (FB)
unnamed: L6.2, U18.3 (LX)
unnamed: R41.1, U19.18 (PSELF)
unnamed: C79.2, U20.6 (V3_{OUT})
VBUS: C62.2, C63.2, C74.2, C78.2, D1.2 (A), D2.2 (A), J7.6, L5.1, L7.2, U13.6 (VIN), U14.6 (VIN), U16.3 (D), U19.19 (V5), U20.3 (VDD5), U20.9 (VBUS)
